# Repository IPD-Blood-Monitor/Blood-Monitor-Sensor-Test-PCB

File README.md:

View this project on [CADLAB.io](https://cadlab.io/project/2247). 

# Blood-Monitor-Sensor-Test-PCB

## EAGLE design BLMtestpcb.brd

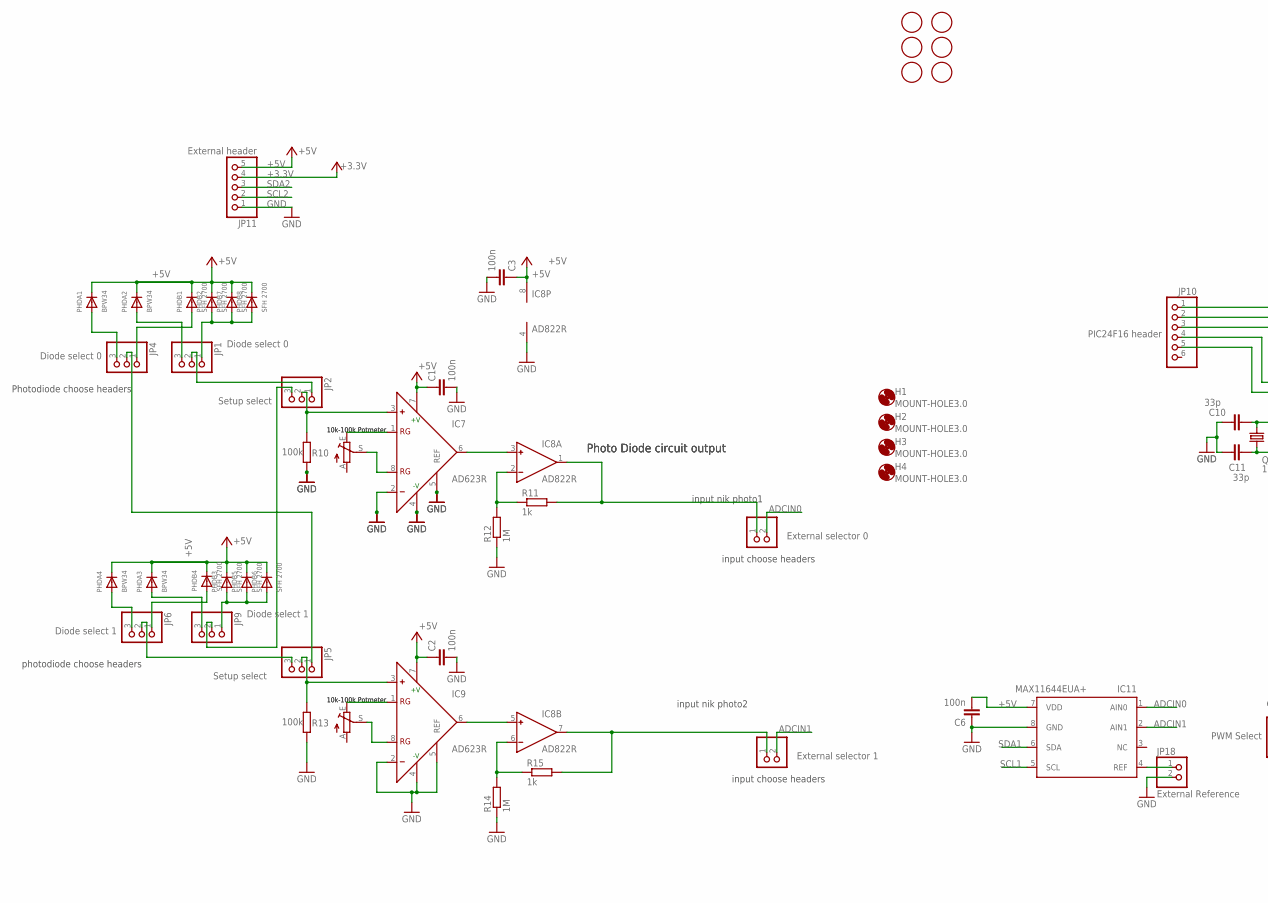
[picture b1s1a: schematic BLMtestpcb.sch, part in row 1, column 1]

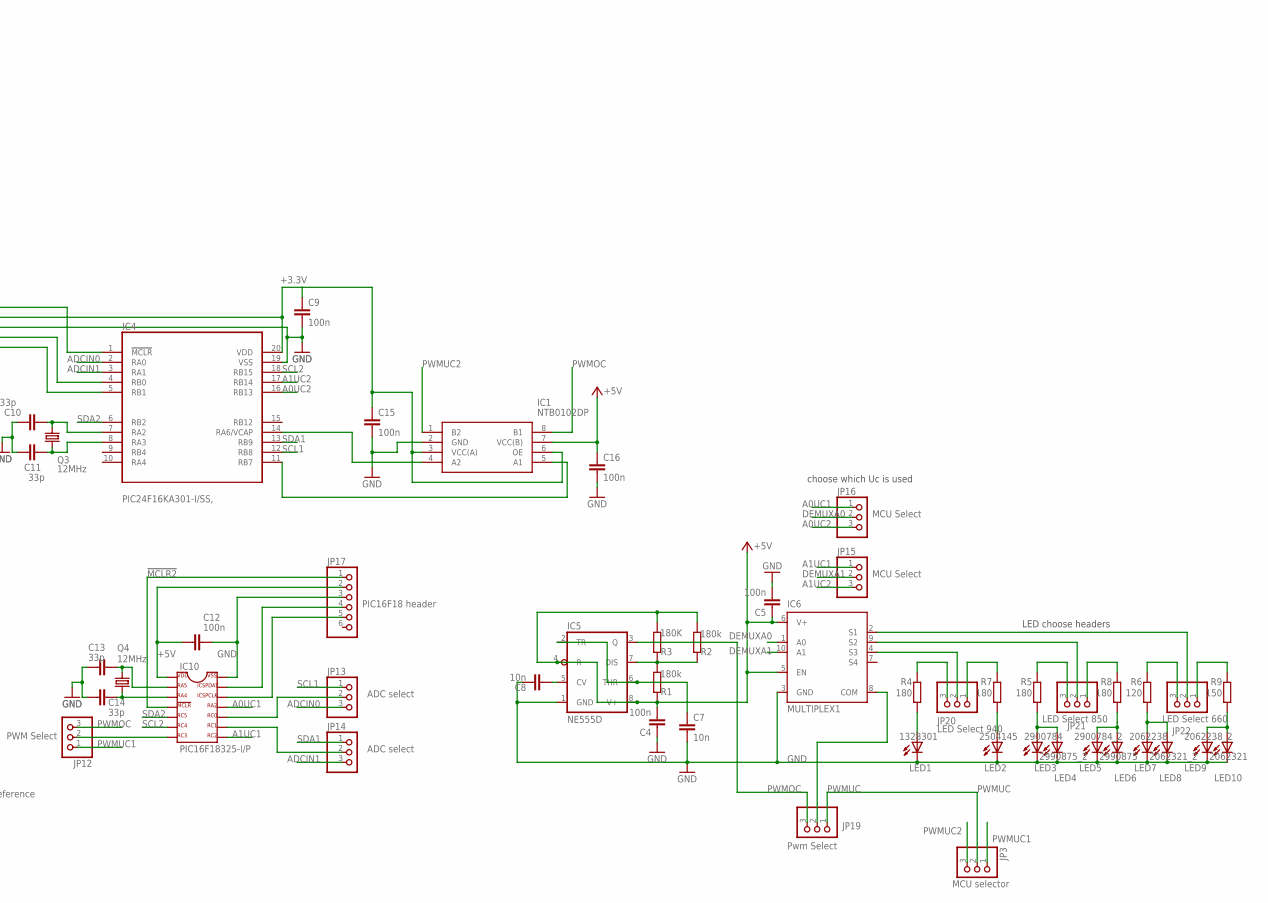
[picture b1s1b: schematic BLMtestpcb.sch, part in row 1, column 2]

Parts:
C1, C2, C3, C4, C5, C6: 100n; C025-025X050
C7, C8: 10n; C025-025X050
C9, C12, C15, C16: 100n; C025-024X044
C10, C11, C13, C14: 33p; C025-025X050
H1, H2, H3, H4: MOUNT-HOLE3.0; 3,0
IC1: NTB0102DP; SOP65P400X110-8N
IC4: PIC24F16KA301-I/SS,; WM8804
IC5: NE555D; SO08
IC6: MULTIPLEX1; MSOP10
IC7, IC9: AD623R; SO8
IC8: AD822R; SO8
IC10: PIC16F18325-I/P; DIL14
IC11: MAX11644EUA+; UMAX8
JP1, JP4: Diode select 0; 1X03
JP2, JP5: Setup select; 1X03
JP3: MCU selector; 1X03
JP6, JP9: Diode select 1; 1X03
JP7: External selector 0; 1X02
JP8: External selector 1; 1X02
JP10: PIC24F16 header; 1X06
JP11: External header; 1X05
JP12: PWM Select; 1X03
JP13, JP14: ADC select; 1X03
JP15, JP16: MCU Select; 1X03
JP17: PIC16F18 header; 1X06
JP18: External Reference; 1X02
JP19: Pwm Select; 1X03
JP20: LED Select 940; 1X03
JP21: LED Select 850; 1X03
JP22: LED Select 660; 1X03
LED1: 1328301; CHIPLED_1206
LED2: 2504145; CHIPLED_1206
LED3: 2900784; CHIPLED_0603
LED4: 2990875_2; CHIPLED_1206
LED5: 2900784_2; CHIPLED_0603
LED6: 2990875; CHIPLED_1206
LED7: 2062238; CHIPLED_0805
LED8: 2062321_2; CHIPLED_1206
LED9: 2062238_2; CHIPLED_0805
LED10: 2062321; CHIPLED_1206
PHDA1, PHDA2, PHDA3, PHDA4: BPW34; SOT23-W
PHDB1, PHDB2, PHDB3, PHDB4, PHDB5, PHDB6, PHDB7, PHDB8: SFH 2700; SOD-123FL
POTMETER1, POTMETER2: 10k-100k; PT-10
Q3, Q4: 12MHz; HC49U70
R1, R2: 180k; 0207/10
R3: 180K; 0207/10
R4, R5, R7, R8: 180; 0207/10
R6: 120; 0207/10
R9: 150; 0207/10
R10, R13: 100k; 0207/10
R11, R15: 1k; 0207/10
R12, R14: 1M; 0207/10
U$1, U$2, U$3, U$4, U$5, U$6: FIDUCIAL; FIDUCIAL_1MM

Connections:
660A: JP22.3, R6.2
660B: JP22.1, R9.2
850A: JP21.3, R5.2
850B: JP21.1, R8.2
940A: JP20.3, R4.2
940B: JP20.1, R7.2
!MCLR: IC4.1 (!MCLR), JP10.1
!MCLR2: IC10.4 (VPP/!MCLR/RA3), JP17.1
+3.3V: C9.1, C15.1, IC1.3 (VCC(A)), IC1.6 (OE), IC4.20 (VDD), JP10.2, JP11.4
+5V: C1.1, C2.1, C3.1, C4.2, C5.1, C6.2, C12.1, IC5.4 (R), IC5.8 (V+), IC6.5 (EN), IC6.6 (V+), IC7.7 (+V), IC8.8 (V+), IC9.7 (+V), IC10.1 (VDD), IC11.7 (VDD), JP11.5, JP17.2, PHDA1.3 (C), PHDA2.3 (C), PHDA3.3 (C), PHDA4.3 (C), PHDB1.C, PHDB2.C, PHDB3.C, PHDB4.C, PHDB5.C, PHDB6.C, PHDB7.C, PHDB8.C, R1.1, R2.2, R3.2
A0UC1: IC10.11 (RA2), JP16.1
A0UC2: IC4.16 (RB13), JP16.3
A1UC1: IC10.8 (RC2), JP15.1
A1UC2: IC4.17 (RB14), JP15.3
ADCIN0: IC4.2 (RA0), IC11.1 (AIN0), JP7.2, JP13.3
ADCIN1: IC4.3 (RA1), IC11.2 (AIN1), JP8.2, JP14.3
BOT0: JP2.3, JP9.2
BOT1: JP5.3, JP6.2
DEMUXA0: IC6.1 (A0), JP16.2
DEMUXA1: IC6.10 (A1), JP15.2
GND: C1.2, C2.2, C3.2, C4.1, C5.2, C6.1, C7.2, C8.1, C9.2, C10.1, C11.1, C12.2, C13.1, C14.1, C15.2, C16.2, IC1.2 (GND), IC4.19 (VSS), IC5.1 (GND), IC6.3 (GND), IC7.2 (-), IC7.4 (-V), IC7.5 (REF), IC8.4 (V-), IC9.2 (-), IC9.4 (-V), IC9.5 (REF), IC10.14 (VSS), IC11.8 (GND), JP10.3, JP11.1, JP17.3, JP18.2, LED1.C, LED2.C, LED3.C, LED4.C, LED5.C, LED6.C, LED7.C, LED8.C, LED9.C, LED10.C, R10.2, R12.1, R13.2, R14.1
INPUTPHOTO1: IC8.1 (OUT), JP7.1, R11.2
unnamed: IC8.6 (IN-), R14.2, R15.1
unnamed: IC1.4 (A2), IC4.14 (RA6/VCAP)
unnamed: IC1.5 (A1), IC4.11 (RB7)
unnamed: C7.1, IC5.2 (TR), IC5.6 (THR)
unnamed: IC5.7 (DIS), R1.2, R2.1, R3.1
unnamed: IC6.8 (COM), JP19.2
unnamed: C8.2, IC5.5 (CV)
unnamed: LED1.A, R4.1
unnamed: LED3.A, LED4.A, R5.1
unnamed: LED7.A, LED8.A, R6.1
unnamed: LED2.A, R7.1
unnamed: LED5.A, LED6.A, R8.1
unnamed: LED9.A, LED10.A, R9.1
unnamed: IC6.2 (S1), JP22.2
unnamed: IC6.9 (S2), JP21.2
unnamed: IC6.4 (S3), JP20.2
unnamed: IC7.1 (RG), POTMETER2.E
unnamed: IC9.1 (RG), POTMETER1.E
unnamed: IC7.6 (OUT), IC8.3 (IN+)
unnamed: IC8.2 (IN-), R11.1, R12.2
unnamed: IC9.8 (RG), POTMETER1.S
unnamed: IC8.5 (IN+), IC9.6 (OUT)
unnamed: IC8.7 (OUT), JP8.1, R15.2
unnamed: IC7.8 (RG), POTMETER2.S
unnamed: IC10.13 (RA0/ICSPDAT), JP17.4
unnamed: IC4.5 (RB1), JP10.5
unnamed: IC4.4 (RB0), JP10.4
unnamed: IC10.12 (RA1/ICSPCLK), JP17.5
unnamed: C10.2, IC4.7 (RA2), Q3.2
unnamed: C11.2, IC4.8 (RA3), Q3.1
unnamed: IC10.7 (RC3), JP12.2
unnamed: C14.2, IC10.3 (RA4), Q4.1
unnamed: C13.2, IC10.2 (RA5), Q4.2
OP-AMP0: IC7.3 (+), JP2.2, R10.1
OP-AMP1: IC9.3 (+), JP5.2, R13.1
PWMOC: IC1.8 (B1), IC5.3 (Q), JP12.3, JP19.3
PWMUC: JP3.2, JP19.1
PWMUC1: JP3.1, JP12.1
PWMUC2: IC1.1 (B2), JP3.3
RC2: IC10.10 (RC0), JP13.2
RC3: IC10.9 (RC1), JP14.2
REF: IC11.4 (REF), JP18.1
SCL1: IC4.12 (RB8), IC11.5 (SCL), JP13.1
SCL2: IC4.18 (RB15), IC10.6 (RC4), JP11.2
SDA1: IC4.13 (RB9), IC11.6 (SDA), JP14.1
SDA2: IC4.6 (RB2), IC10.5 (RC5), JP11.3
TOP0: JP1.2, JP2.1
TOP1: JP4.2, JP5.1
TYPE00A: JP4.3, PHDA1.1 (A), PHDA1.2 (A)
TYPE00B: JP4.1, PHDB1.A
TYPE01A: JP1.3, PHDA2.1 (A), PHDA2.2 (A)
TYPE01B: JP1.1, PHDB2.A, PHDB7.A, PHDB8.A
TYPE10A: JP6.3, PHDA4.1 (A), PHDA4.2 (A)
TYPE10B: JP6.1, PHDB4.A
TYPE11A: JP9.3, PHDA3.1 (A), PHDA3.2 (A)
TYPE11B: JP9.1, PHDB3.A, PHDB5.A, PHDB6.A
VCC: C16.1, IC1.7 (VCC(B))

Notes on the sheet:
Photo Diode circuit output
10k-100k Potmeter
input nik photo1
input nik photo2
Photodiode choose headers
photodiode choose headers
input choose headers
LED choose headers
choose which Uc is used

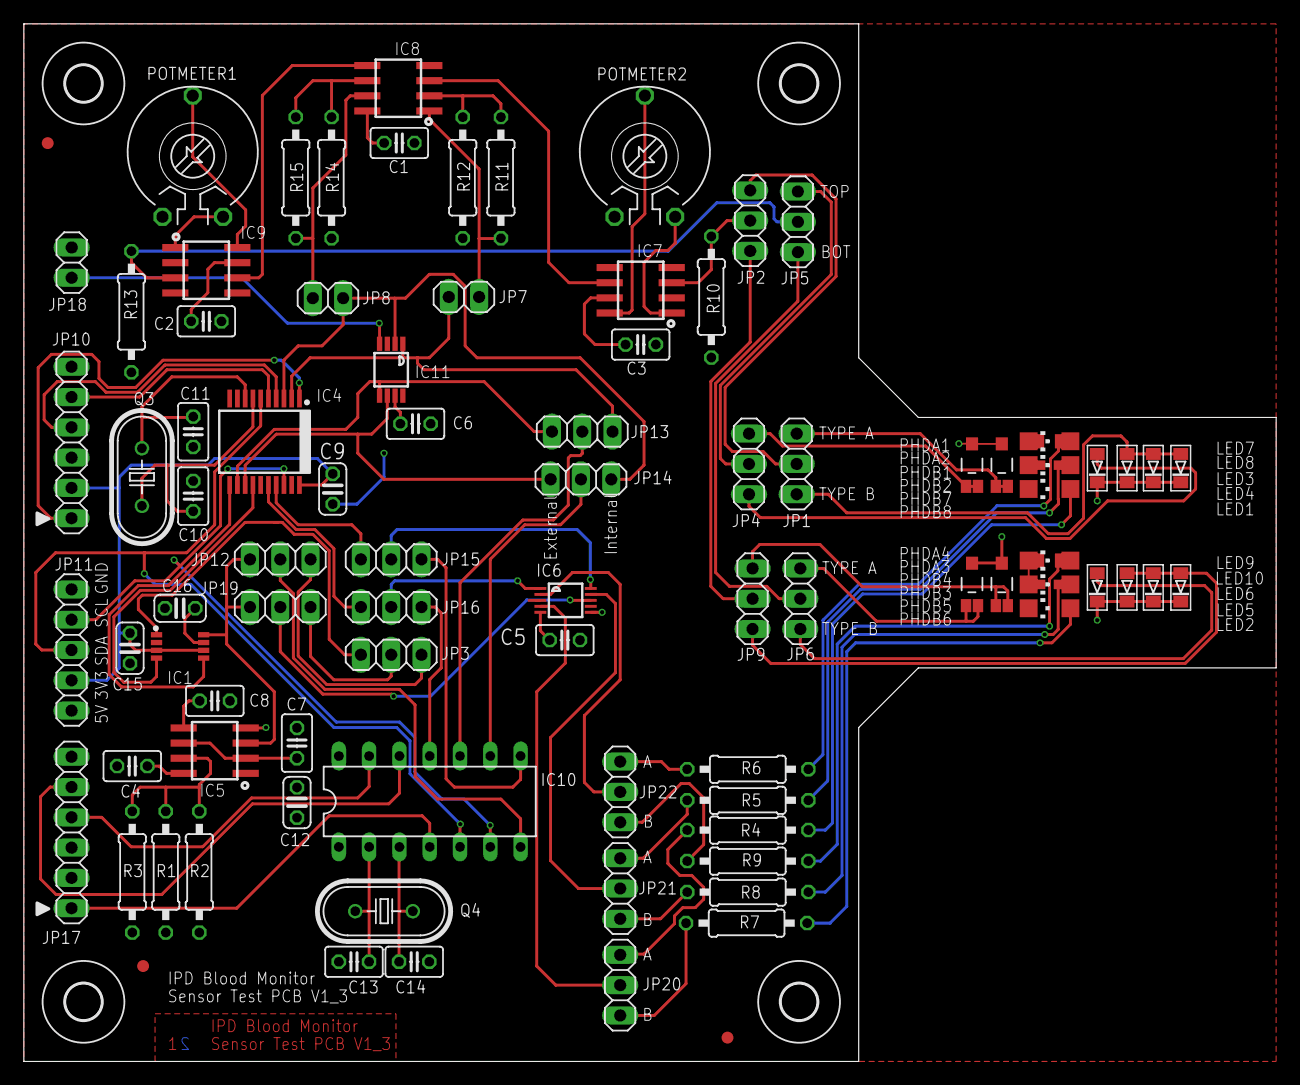
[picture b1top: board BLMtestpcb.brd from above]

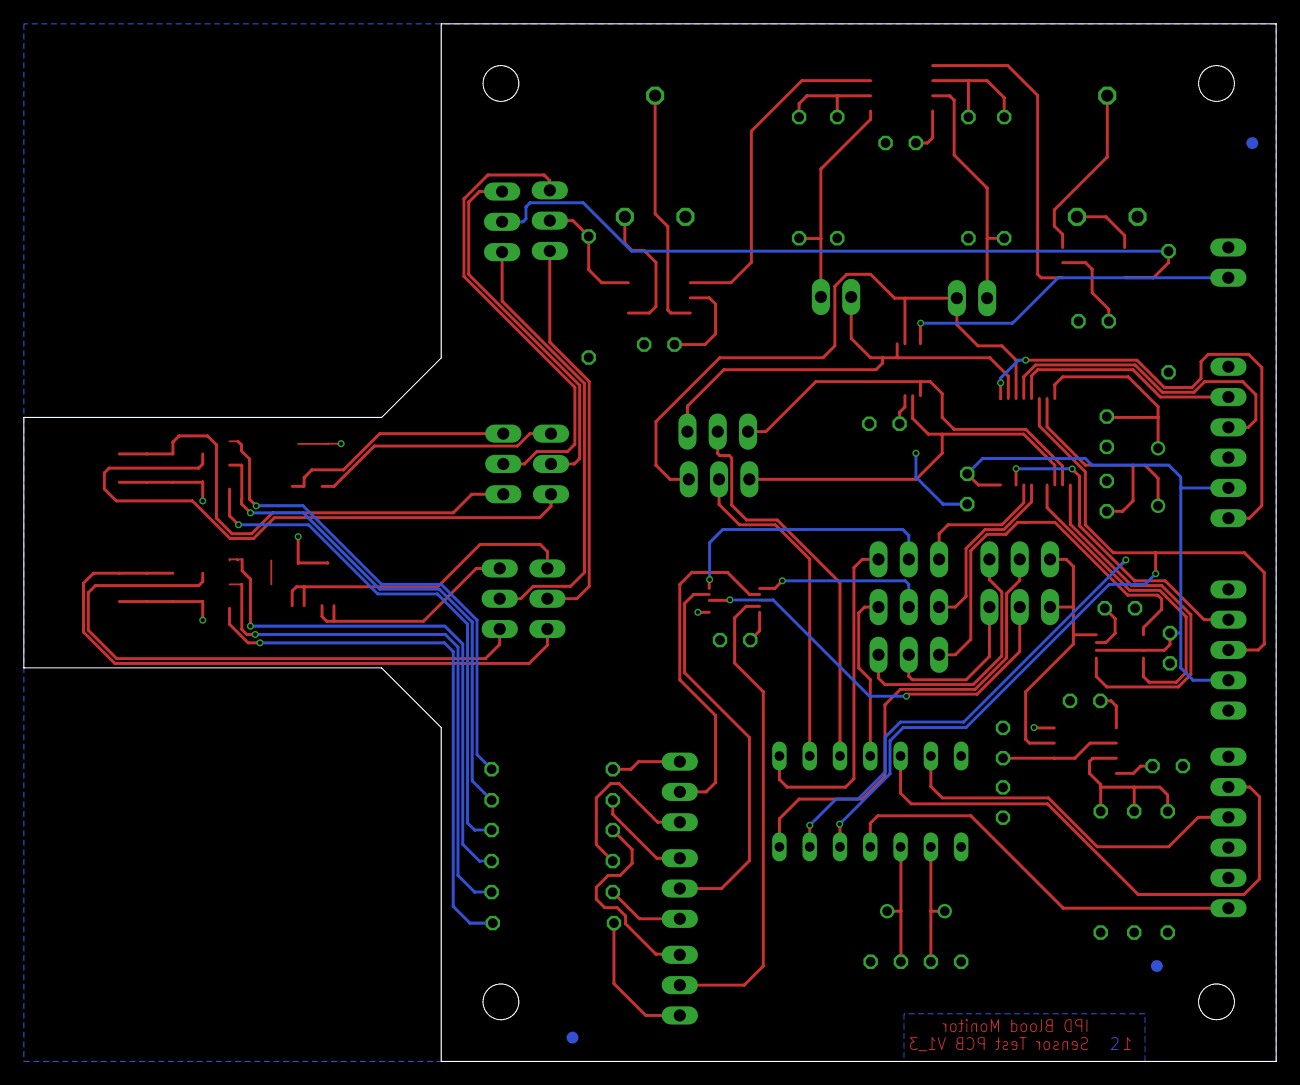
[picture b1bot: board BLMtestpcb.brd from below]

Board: 2 copper layers, 105.0 x 87.0 mm, 98 parts (3 on the bottom side), 79 nets.

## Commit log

2019-10-25 Backlink to CADLAB.io has been added.
2019-10-25 Initial V1 commit
2019-10-29 Renamed files
2019-11-14 Update to v1_3
    Change some component footprints to have pin 1 indication. Remove 1mm length difference in PCB
